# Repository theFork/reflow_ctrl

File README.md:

# Reflow Controller
A simple-as-possible reflow oven controller. It uses the [uMIDI](https://github.com/theFork/uMIDI) board and library as microcontroller and for USB host communication.

* 3.3V and 5V sourced from the controller board (uMIDI)
* Solid state relais Finder 77.11..9.8251 (15A) to power an oven from a low current 5V signal
* AD converter (MAX6675), connected to type-K thermocoupler
* Graphical host software written in Java

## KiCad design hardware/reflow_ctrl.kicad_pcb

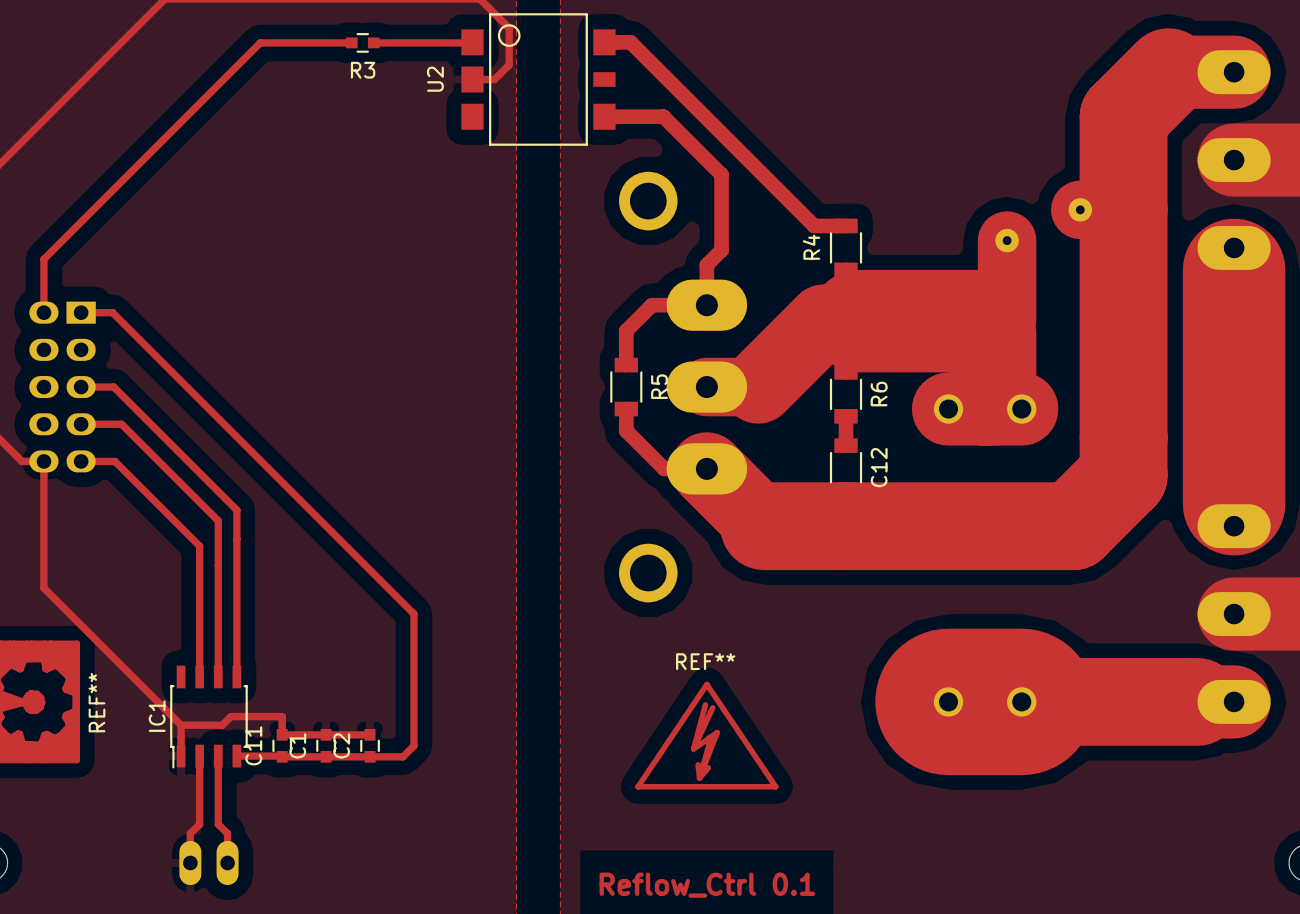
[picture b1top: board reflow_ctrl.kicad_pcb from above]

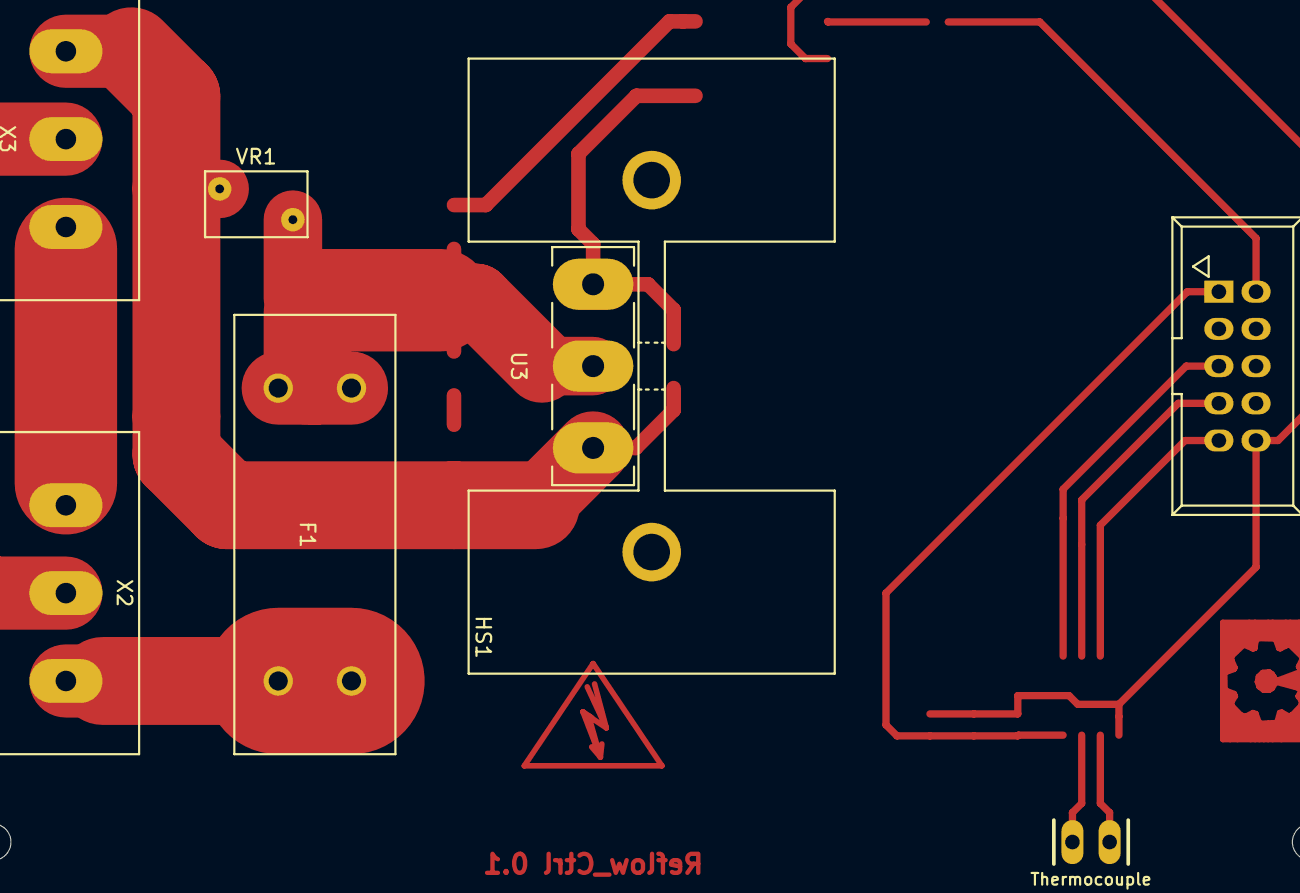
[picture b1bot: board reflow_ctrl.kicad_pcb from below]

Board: 2 copper layers, 18 parts (8 on the bottom side), 16 nets.

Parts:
C1, C2, C11: 100n; Pas_0603
C12: 10n; Pas_1206
F1: Insert 12A slow; Fuseholder_Schurter_20x5
HS1: HEATSINK; Mech-Heatsink_Fischer_SK129_STS
IC1: MAX6675; SOIC-8_3.9x4.9mm_Pitch1.27mm
R3: 390; Pas_0603
R4, R5: 360; Pas_1206
R6: 39; Pas_1206
U2: MOC3063; Semi-Optotriac_MOC3063-SMD
U3: BTA41/600B; TO-247_Vertical_Neutral123_largePads
VR1: 430V; RV_Disc_D7_W4.5_P5
X1: Master; Con-boxed_header-THT
X2: Mains; Mains_Solder
X3: Load; Mains_Solder
X4: Thermocouple; Pinhead1-2

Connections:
+3V3: C1.1, C2.1, C11.1, IC1.4, X1.1
/L_load: C12.2, R5.2, U3.1, VR1.2, X3.1
/L_main_fused: F1.1, R4.1, R6.1, U3.2, VR1.1
/L_mains: F1.2, X2.1
/MOC_A1: R4.2, U2.6
/MOC_A2: R5.1, U2.4, U3.3
/N_mains: X2.3, X3.3
/PE_mains: X2.2, X3.2
/PWR: R3.2, X1.2
/Snub: C12.1, R6.2
/TC+: IC1.3, X4.1
/TC_SCK: IC1.5, X1.5
/TC_SO: IC1.7, X1.9
/~TC_CS: IC1.6, X1.7
GND: C1.2, C2.2, C11.2, IC1.1, IC1.2, U2.2, X1.10, X4.2
unnamed: R3.1, U2.1

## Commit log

2016-01-31 Initial commit with concept
2016-01-31 Initial schematic
2016-01-31 Add uMIDI.pretty footprints module
2016-01-31 Assign some footprints
2016-01-31 Move protection earth between L and N
2016-01-31 Add and assign mains terminal footprint
2016-01-31 Add supplier links and optotriac footprint
2016-02-01 Sanetize output circuit; Add varistor
2016-02-01 Add fuse holder footprint
2016-02-01 Assign all footprints
2016-02-01 Initial placement; Select pcb outline; Add TODO
2016-02-03 Use big USB-B THT connector
2016-02-15 Remove MCU circuit (use external uMIDI)
2016-02-15 ERC clean
2016-02-15 Update uMIDI.pretty: Fix footprint syntax (?)
2016-02-15 Add project specific library description
2016-02-15 Update board
2016-02-15 Prepare net classes
2016-02-19 Revise readme
2016-02-19 Shrink schematic page size
2016-02-19 Add mounting holes
2016-02-19 Disentangle connector pinout; Start placement
2016-02-19 Add and use uMIDI.pretty generic smd packages
2016-02-19 Place and lock heatsink and triac
2016-02-19 Start place and route
2016-02-20 Revise placement; Route
2016-02-20 Finish routing
2016-02-20 Edit optotriac package; DRC clean
2016-02-20 Connect heatsink to PE
2016-02-21 Use a smaller VDR package
2016-02-21 Optimize header pinout and trace widths
2016-02-21 Add some fancy symbols
2016-06-24 Add first draft of the software spec
2016-06-24 Add uMIDI submodule
2016-06-24 Copy firmware template and adapt makefile
2016-06-24 Make it compile; Add gitignore
2016-06-24 Remove Doxygen template
2016-06-25 Improve formatting on software specification
2016-06-25 Fix missing GND on TC-
2016-06-25 Add CLI skeleton
2016-06-25 Update uMidi submodule and include SPI module in build
2016-06-25 Configure SPI module
2016-06-25 Implement heating function and shot command
2016-06-25 Implement temperature readout
2016-06-25 Implement temperature offset calibration via CLI
2016-07-01 Implement communicator
2016-07-04 Add jfreegraph lib; Create proof of concept class
2016-07-07 Embedd into a JFrame
2016-07-19 Use packages
2016-07-19 Externalize (stub) plot data
2016-07-20 Add project specific formatters
2016-07-20 Make transceive private; Stub access methods
2016-07-20 Apply formatter; Stub menu bar
2016-07-20 Extend JFrame; Use event queue to display window
2016-07-20 Suppress serial warnings; Remove @author lines
2016-07-20 Implement File->Quit action
2016-07-20 Implement generic PID controller and control loop task dummy
2016-07-24 Tweak and simplify chart
2016-07-24 Implement and integrate profile reader
2016-07-24 Add status bar
2016-07-24 Integrate status bar
2016-07-24 Update uMIDI submodule
2016-07-24 Communicator: Fix / finish getTemperature() and shot()
2016-07-24 Finish main control task logic
2016-07-24 Controller: Save P-, I-, and D-terms and make them accessible
2016-07-24 DataLogger: Add optional PID controller debug traces
2016-07-24 Fix integer overflow in echo of exec_shot()
2016-07-29 Prepare Help-Info
2016-07-29 Prepare checkbox 'Plot internals'
2016-09-15 Implement info message
2016-09-24 Ignore lines that are not comma separated
2016-09-24 Remove menu bar
2016-09-24 Show temperature profile from the beginning
2016-10-04 Modify profile for first tests
2016-10-04 Remove measurement test code
2016-10-04 Do not send shots < 0
2016-10-04 Fix isConnected status bar item
2016-10-07 Move all sources to recycler package
2016-10-07 Stub mvc main classes
2016-10-07 Stub model
2016-10-07 Make profile a static method returning XYSeries
2016-10-07 Stub control runnable
2016-10-07 Add button bar; Stub action listeners
2016-10-07 Reinitiae executor on click run
2016-10-08 Generate and add chart panel
2016-10-08 Manage temperature measurement and plotting
2016-10-08 Read the temperature 5 times and return average
2016-10-08 Remove recycler package, saving the status bar
2016-10-08 Bypass global model method getCurrentTemperature
2016-10-08 Implement duty cycle calculation; Fire shots
2016-10-08 Plot duty cycle
2016-10-08 Log using java.util.logging
2016-10-08 Refine connection/disconnection
2016-10-15 Fix port opening
2016-10-15 Warn if there are major temperature differences
2016-10-15 Add shot duration minimum to linear range
2016-10-15 Add and use initial pb-free profile
2016-10-15 Don't warn on empty lines in profile
2016-10-15 Make profile more realistic for the oven
2016-10-15 Finally, use the status bar
2016-10-15 Clear previously recorded series when restarting
2016-10-15 Revise control parameters
2016-10-15 Slow down heating phases
2016-10-15 Create and use profile including new statement
2016-10-15 Refactor TemperatureProfileReader
2016-10-15 More refactoring; Rename to TemperatureProfile
2016-10-15 Implement parsing of linear function lines
2016-10-22 Adapt pb-free profile
2016-10-22 Add short sleep after opening connection
2016-10-22 Make reflow profile realistic for the oven
2016-10-22 Use two-point control approach
2016-10-22 Increase temperature peak duration
2016-10-24 Configure flowctrl and baudrate
2016-10-24 Warn if connect method retuns false
2016-10-25 Add line/shape custumization
2016-10-25 Rework runnable start/stop mechanism
2016-10-25 Yet again - Edit profile
2016-10-28 WIP: Fix submodule (?)
